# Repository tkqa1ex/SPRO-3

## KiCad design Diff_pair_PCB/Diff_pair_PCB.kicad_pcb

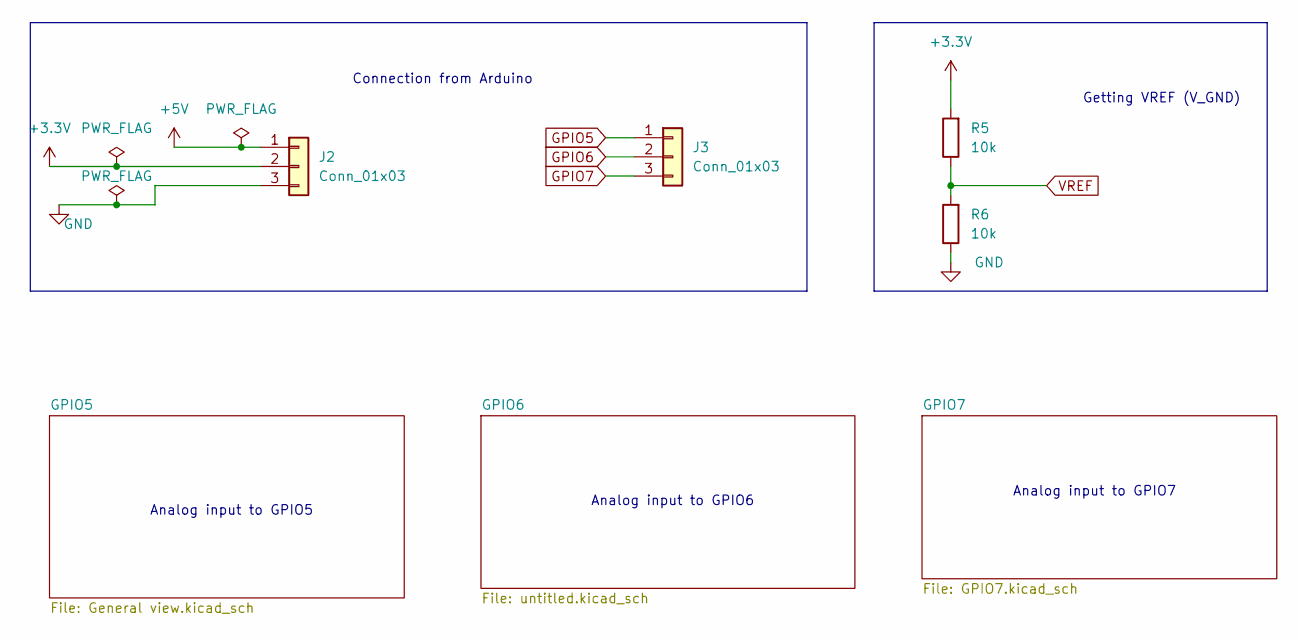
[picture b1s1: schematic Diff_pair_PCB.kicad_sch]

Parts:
J2, J3: Conn_01x03; PinHeader_1x03_P2.54mm_Vertical
R5, R6: 10k; R_Axial_DIN0207_L6.3mm_D2.5mm_P7.62mm_Horizontal

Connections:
+3.3V: J2.2, R5.2; also elsewhere on the board
+5V: J2.1; also elsewhere on the board
GND: J2.3, R6.1; also elsewhere on the board
GPIO5: J3.1; also elsewhere on the board
GPIO6: J3.2; also elsewhere on the board
GPIO7: J3.3; also elsewhere on the board
VREF: R5.1, R6.2; also elsewhere on the board

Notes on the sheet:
Analog input to GPIO7
Analog input to GPIO5
Connection from Arduino
Getting VREF (V_GND)
Analog input to GPIO6

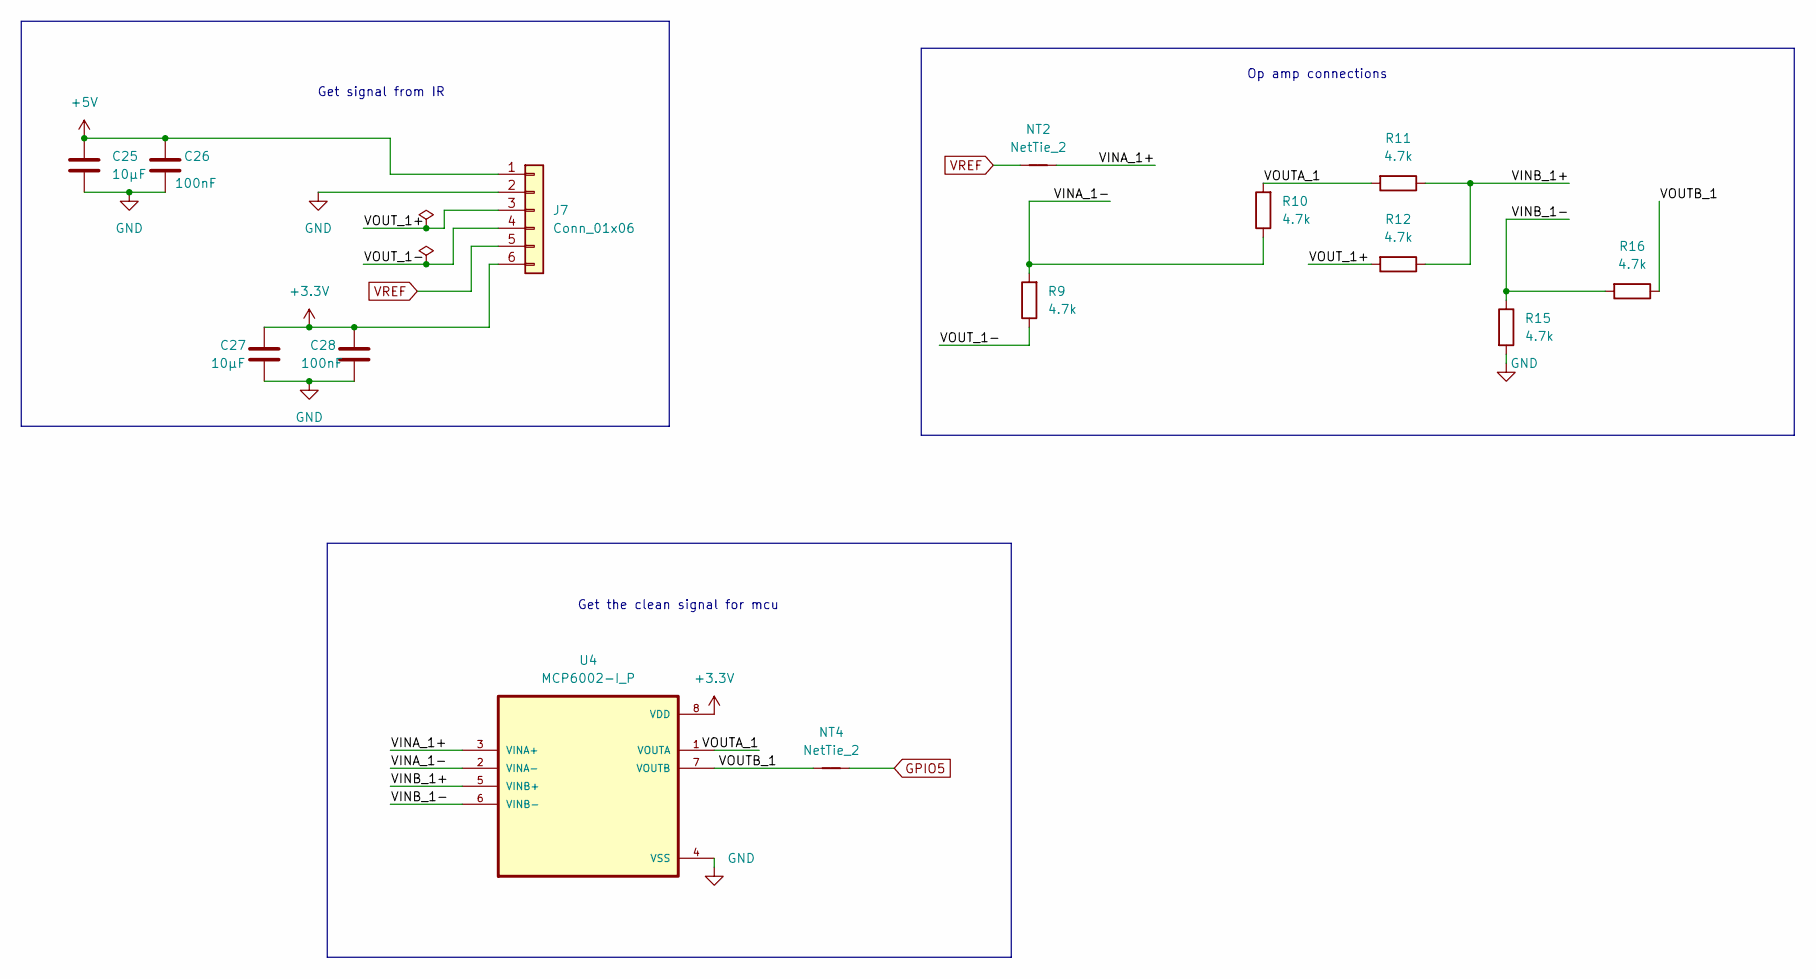
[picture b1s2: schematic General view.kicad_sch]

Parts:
C25, C27: 10µF; CP_Radial_D5.0mm_P2.00mm
C26, C28: 100nF; C_Disc_D5.0mm_W2.5mm_P5.00mm
J7: Conn_01x06; PinHeader_1x06_P2.54mm_Vertical
NT2, NT4: NetTie_2; NetTie-2_SMD_Pad0.3mm
R9, R10, R11, R12, R15, R16: 4.7k; R_Axial_DIN0207_L6.3mm_D2.5mm_P7.62mm_Horizontal
U4: MCP6002-I_P; DIP787W46P254L927H533Q8; MPN MCP6002-I/P

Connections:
+3.3V: C27.1, C28.1, J7.6, U4.8 (VDD); also elsewhere on the board
+5V: C25.1, C26.1, J7.1; also elsewhere on the board
/GPIO5/VINA_1+: NT2.2, U4.3 (VINA+)
/GPIO5/VINA_1-: R9.2, R10.1, U4.2 (VINA-)
/GPIO5/VINB_1+: R11.1, R12.1, U4.5 (VINB+)
/GPIO5/VINB_1-: R15.1, R16.2, U4.6 (VINB-)
/GPIO5/VOUTA_1: R10.2, R11.2, U4.1 (VOUTA)
/GPIO5/VOUTB_1: NT4.1, R16.1, U4.7 (VOUTB)
/GPIO5/VOUT_1+: J7.3, R12.2
/GPIO5/VOUT_1-: J7.4, R9.1
GND: C25.2, C26.2, C27.2, C28.2, J7.2, R15.2, U4.4 (VSS); also elsewhere on the board
GPIO5: NT4.2; also elsewhere on the board
VREF: J7.5, NT2.1; also elsewhere on the board

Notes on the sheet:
Op amp connections
Get signal from IR
Get the clean signal for mcu

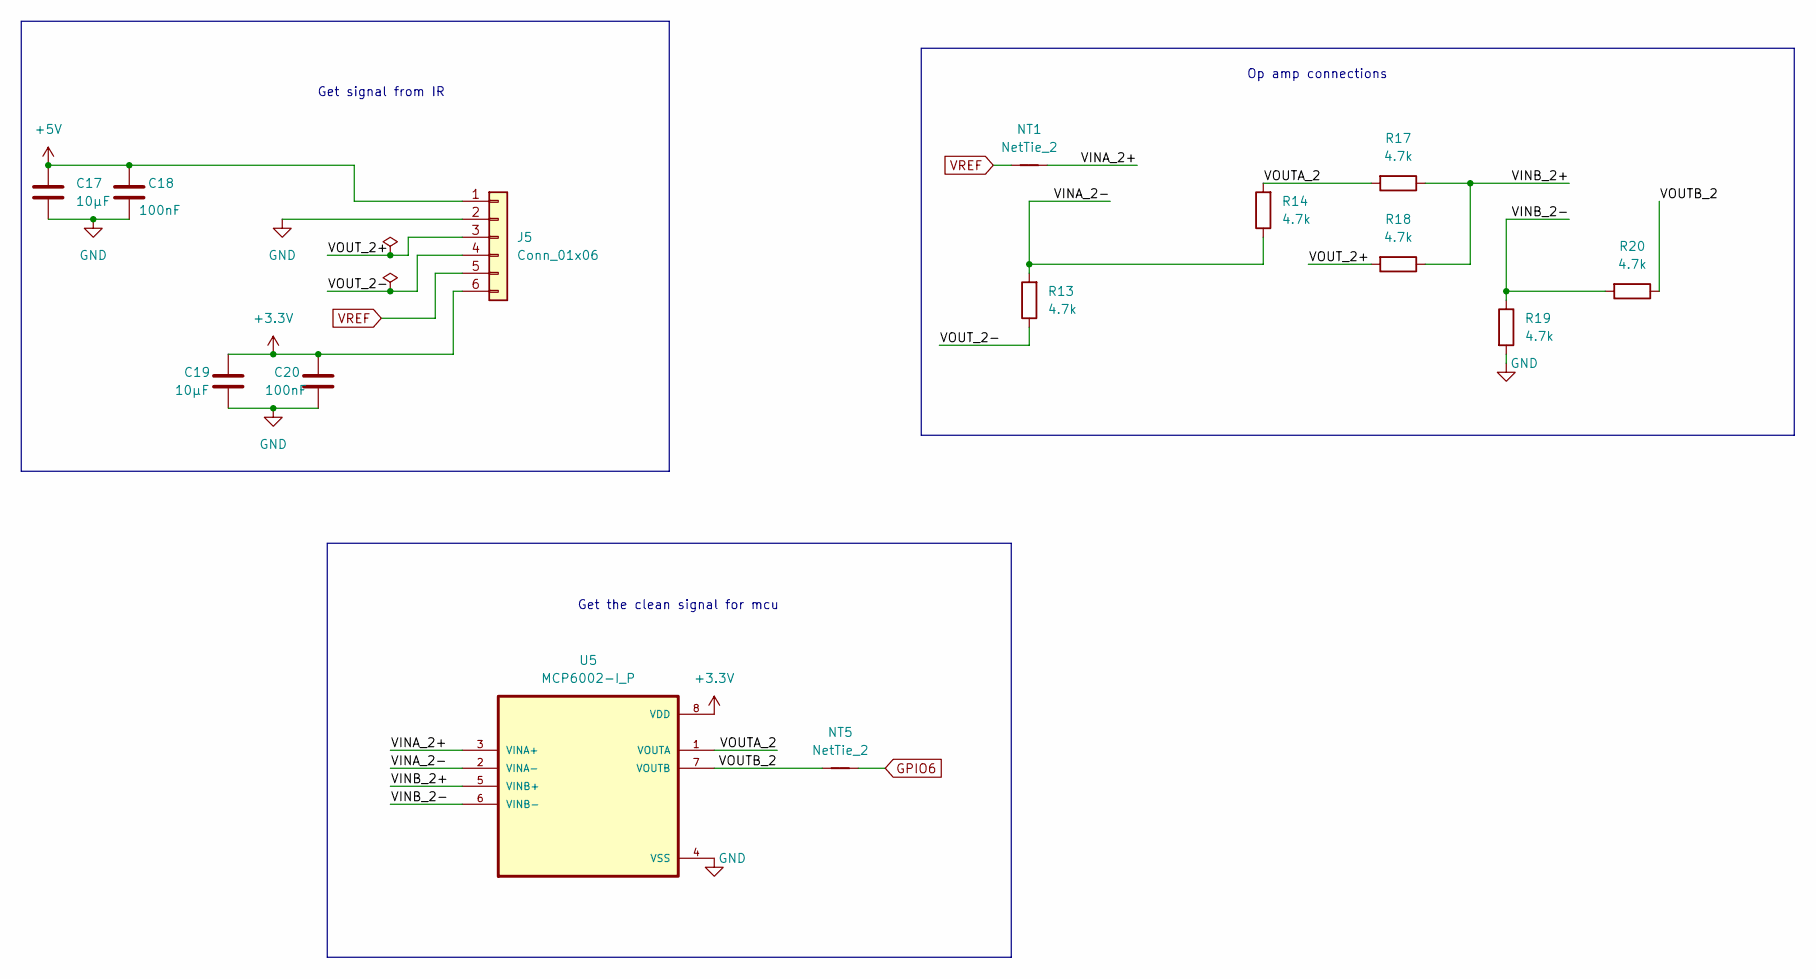
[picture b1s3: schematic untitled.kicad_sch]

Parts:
C17, C19: 10µF; CP_Radial_D5.0mm_P2.00mm
C18, C20: 100nF; C_Disc_D5.0mm_W2.5mm_P5.00mm
J5: Conn_01x06; PinHeader_1x06_P2.54mm_Vertical
NT1, NT5: NetTie_2; NetTie-2_SMD_Pad0.3mm
R13, R14, R17, R18, R19, R20: 4.7k; R_Axial_DIN0207_L6.3mm_D2.5mm_P7.62mm_Horizontal
U5: MCP6002-I_P; DIP787W46P254L927H533Q8; MPN MCP6002-I/P

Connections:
+3.3V: C19.1, C20.1, J5.6, U5.8 (VDD); also elsewhere on the board
+5V: C17.1, C18.1, J5.1; also elsewhere on the board
/GPIO6/VINA_2+: NT1.2, U5.3 (VINA+)
/GPIO6/VINA_2-: R13.2, R14.1, U5.2 (VINA-)
/GPIO6/VINB_2+: R17.1, R18.1, U5.5 (VINB+)
/GPIO6/VINB_2-: R19.1, R20.2, U5.6 (VINB-)
/GPIO6/VOUTA_2: R14.2, R17.2, U5.1 (VOUTA)
/GPIO6/VOUTB_2: NT5.1, R20.1, U5.7 (VOUTB)
/GPIO6/VOUT_2+: J5.3, R18.2
/GPIO6/VOUT_2-: J5.4, R13.1
GND: C17.2, C18.2, C19.2, C20.2, J5.2, R19.2, U5.4 (VSS); also elsewhere on the board
GPIO6: NT5.2; also elsewhere on the board
VREF: J5.5, NT1.1; also elsewhere on the board

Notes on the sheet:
Get the clean signal for mcu
Op amp connections
Get signal from IR

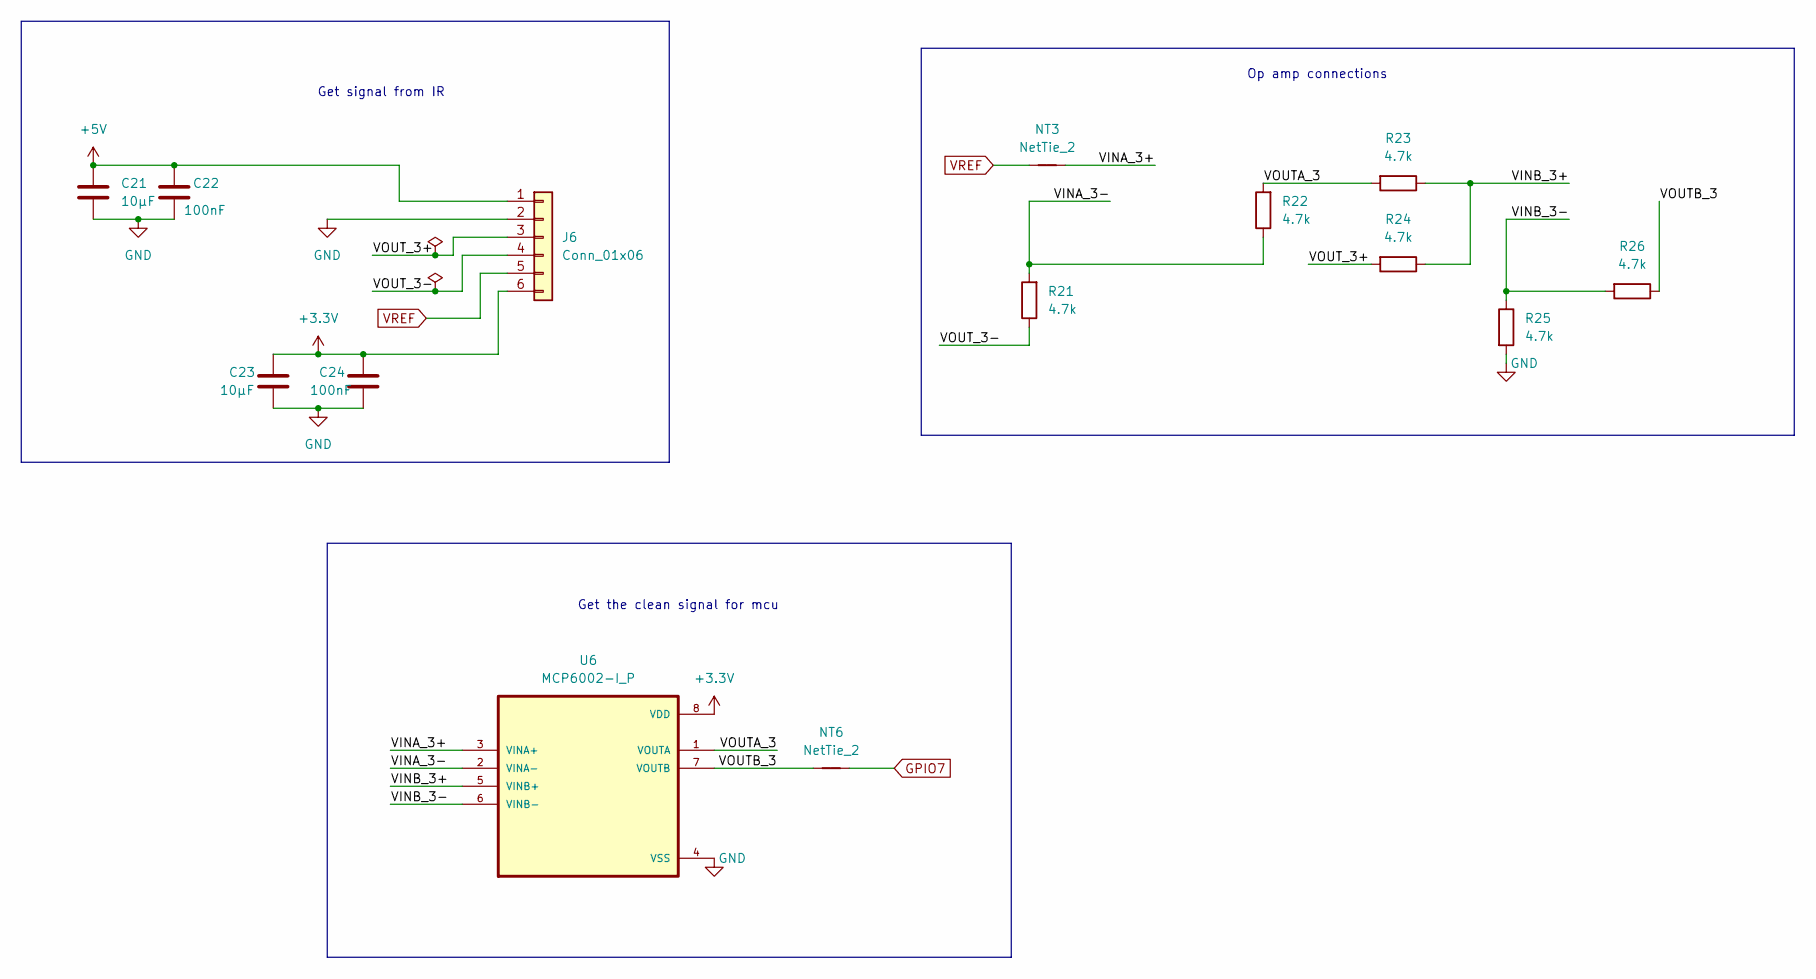
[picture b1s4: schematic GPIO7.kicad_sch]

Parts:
C21, C23: 10µF; CP_Radial_D5.0mm_P2.00mm
C22, C24: 100nF; C_Disc_D5.0mm_W2.5mm_P5.00mm
J6: Conn_01x06; PinHeader_1x06_P2.54mm_Vertical
NT3, NT6: NetTie_2; NetTie-2_SMD_Pad0.3mm
R21, R22, R23, R24, R25, R26: 4.7k; R_Axial_DIN0207_L6.3mm_D2.5mm_P7.62mm_Horizontal
U6: MCP6002-I_P; DIP787W46P254L927H533Q8; MPN MCP6002-I/P

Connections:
+3.3V: C23.1, C24.1, J6.6, U6.8 (VDD); also elsewhere on the board
+5V: C21.1, C22.1, J6.1; also elsewhere on the board
/GPIO7/VINA_3+: NT3.2, U6.3 (VINA+)
/GPIO7/VINA_3-: R21.2, R22.1, U6.2 (VINA-)
/GPIO7/VINB_3+: R23.1, R24.1, U6.5 (VINB+)
/GPIO7/VINB_3-: R25.1, R26.2, U6.6 (VINB-)
/GPIO7/VOUTA_3: R22.2, R23.2, U6.1 (VOUTA)
/GPIO7/VOUTB_3: NT6.1, R26.1, U6.7 (VOUTB)
/GPIO7/VOUT_3+: J6.3, R24.2
/GPIO7/VOUT_3-: J6.4, R21.1
GND: C21.2, C22.2, C23.2, C24.2, J6.2, R25.2, U6.4 (VSS); also elsewhere on the board
GPIO7: NT6.2; also elsewhere on the board
VREF: J6.5, NT3.1; also elsewhere on the board

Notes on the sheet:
Get the clean signal for mcu
Get signal from IR
Op amp connections

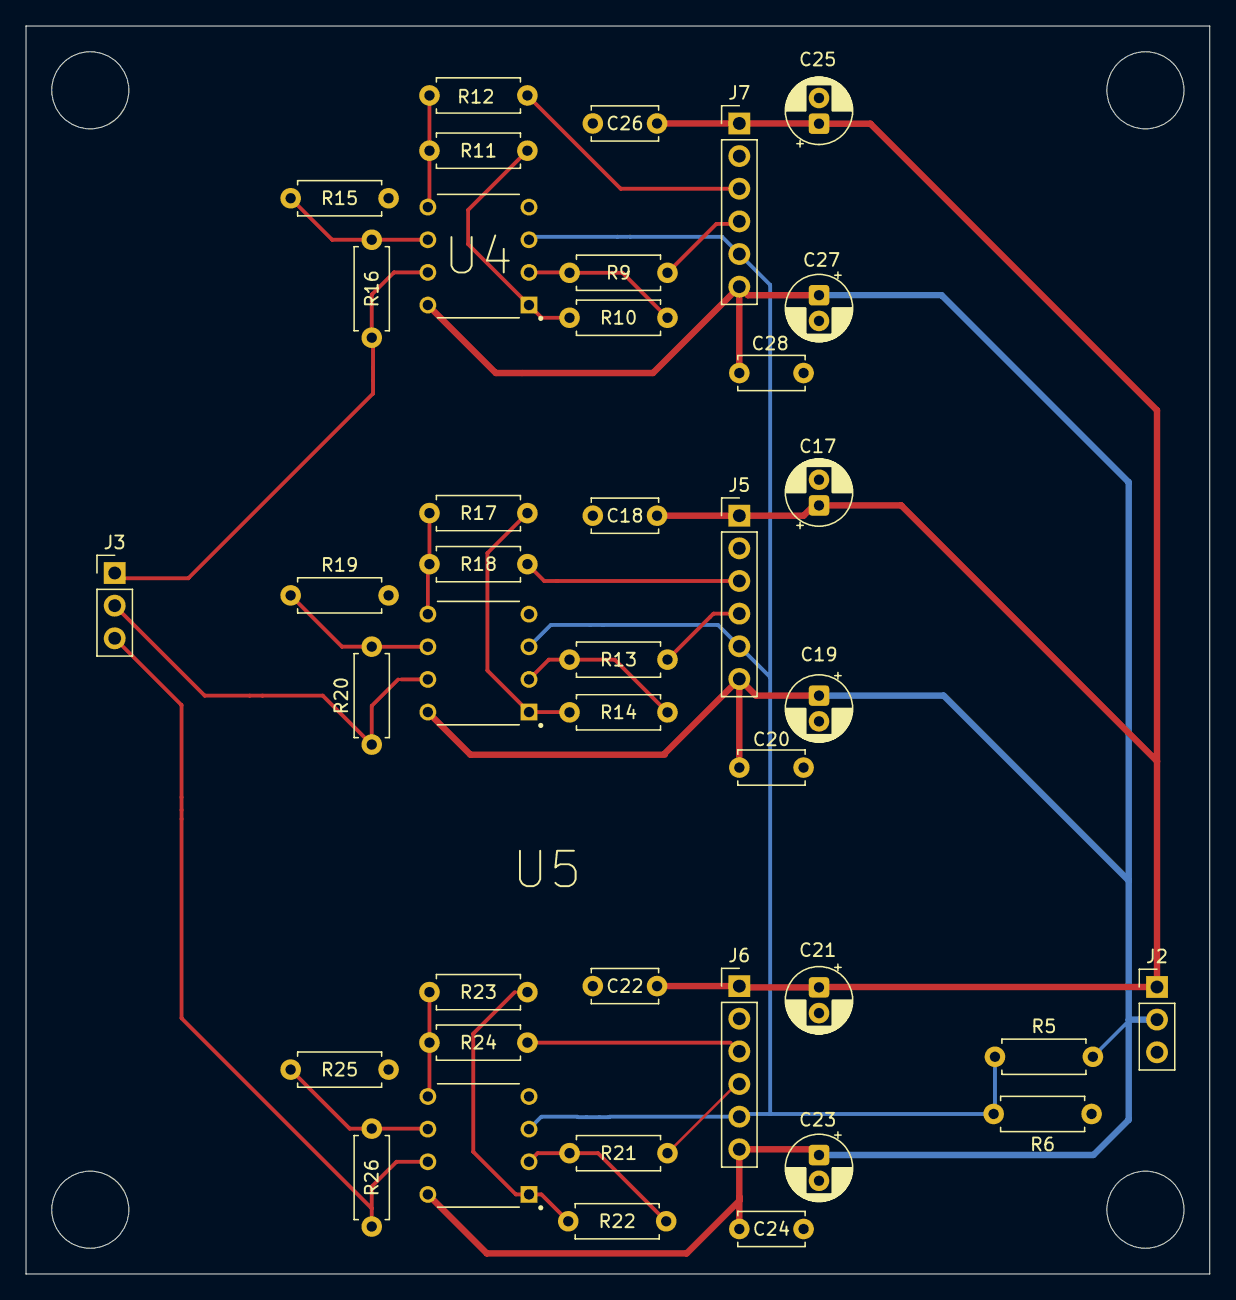
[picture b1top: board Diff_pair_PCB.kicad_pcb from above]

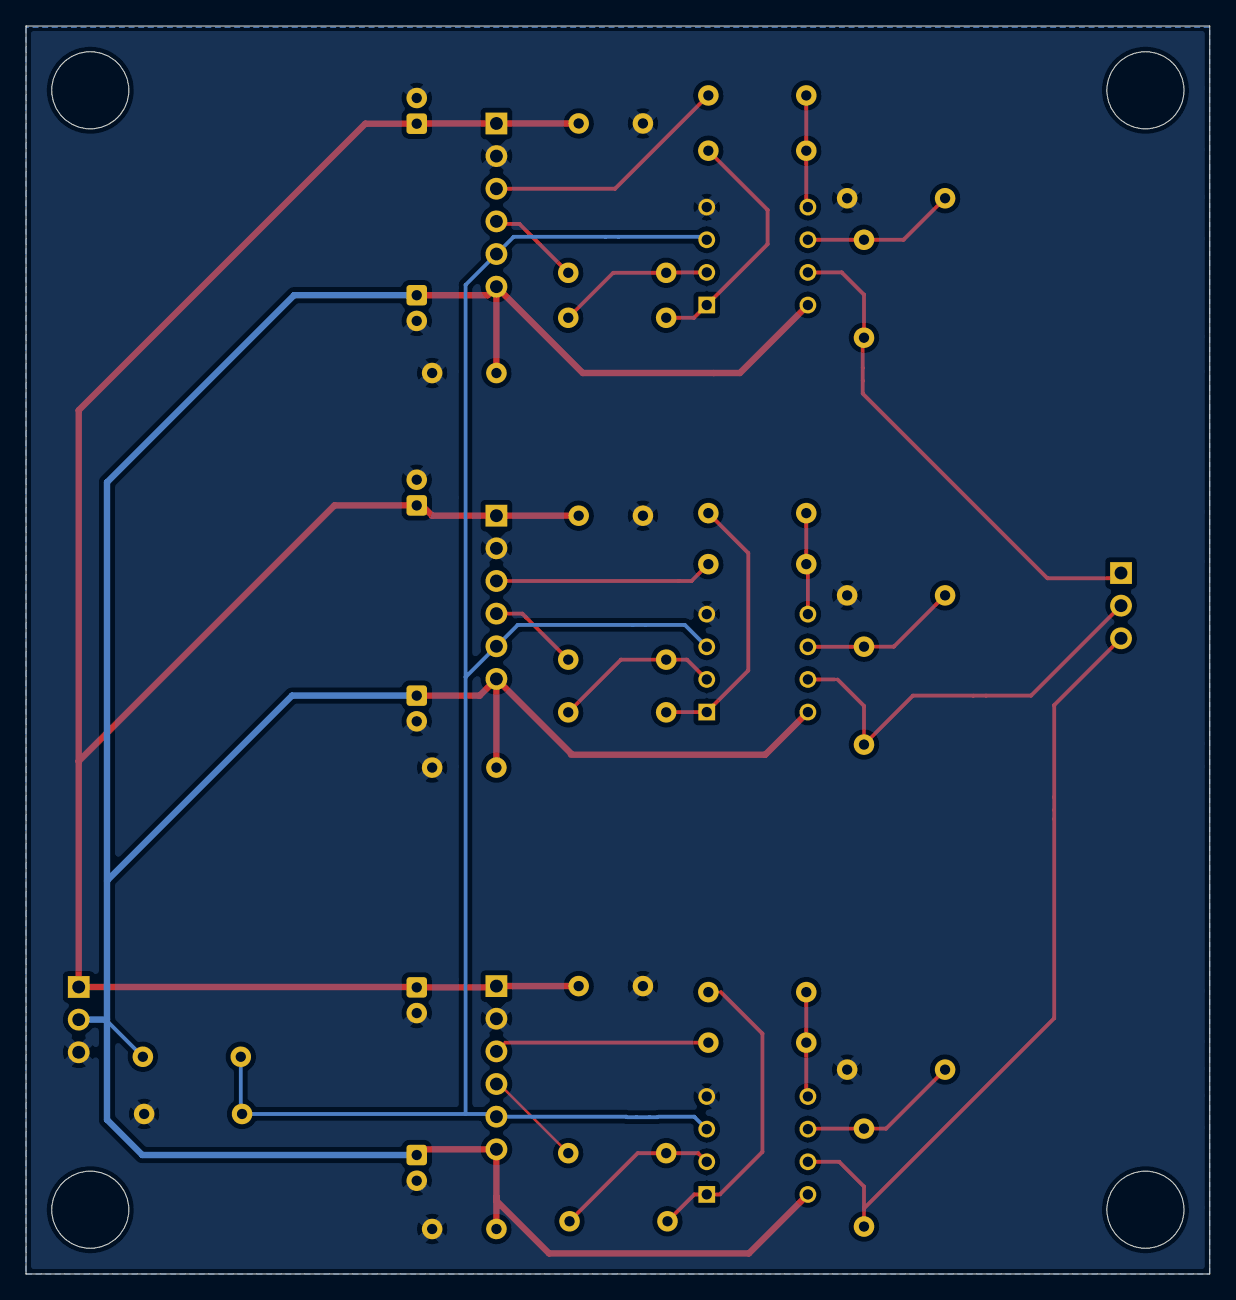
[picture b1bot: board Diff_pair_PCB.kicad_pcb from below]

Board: 2 copper layers, 92.1 x 97.1 mm, 46 parts (3 on the bottom side), 31 nets.

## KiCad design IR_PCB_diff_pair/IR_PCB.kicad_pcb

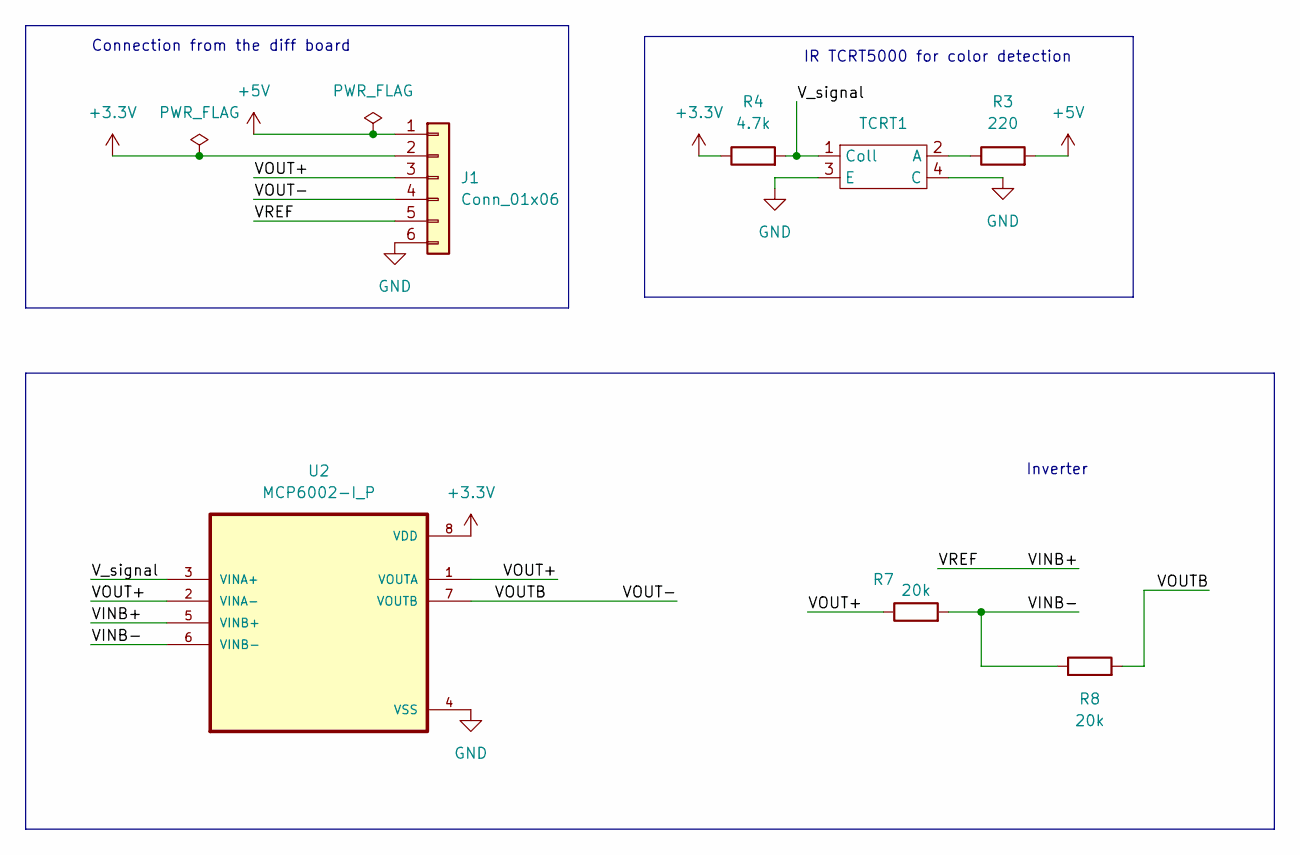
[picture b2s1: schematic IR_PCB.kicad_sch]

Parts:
J1: Conn_01x06; PinHeader_1x06_P2.54mm_Vertical
R3: 220; R_Axial_DIN0207_L6.3mm_D2.5mm_P7.62mm_Horizontal
R4: 4.7k; R_Axial_DIN0207_L6.3mm_D2.5mm_P7.62mm_Horizontal
R7, R8: 20k; R_Axial_DIN0207_L6.3mm_D2.5mm_P7.62mm_Horizontal
TCRT1: TCRT5000L
U2: MCP6002-I_P; DIP787W46P254L927H533Q8; MPN MCP6002-I/P

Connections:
+3.3V: J1.2, R4.1, U2.8 (VDD)
+5V: J1.1, R3.2
/VINB+: J1.5, U2.5 (VINB+)
/VINB-: R7.2, R8.1, U2.6 (VINB-)
/VOUT+: J1.3, R7.1, U2.1 (VOUTA), U2.2 (VINA-)
/VOUT-: J1.4, R8.2, U2.7 (VOUTB)
/V_signal: R4.2, TCRT1.1 (Coll), U2.3 (VINA+)
GND: J1.6, TCRT1.3 (E), TCRT1.4 (C), U2.4 (VSS)
unnamed: R3.1, TCRT1.2 (A)

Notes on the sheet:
Inverter
Connection from the diff board
IR TCRT5000 for color detection

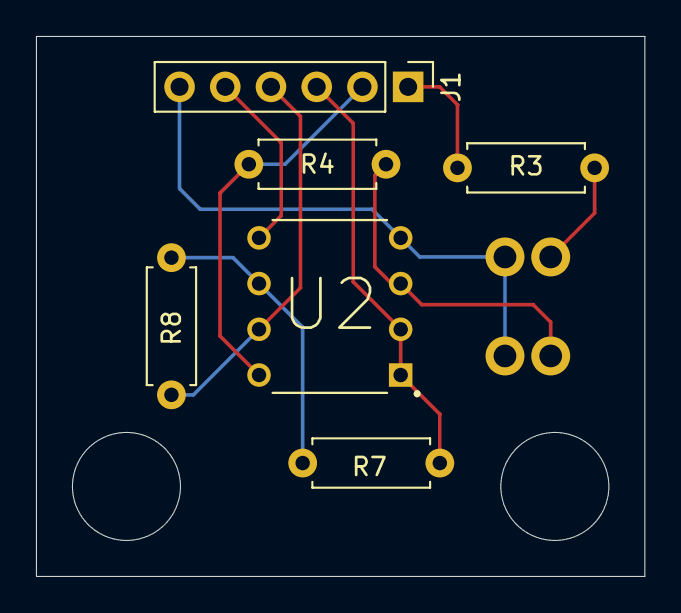
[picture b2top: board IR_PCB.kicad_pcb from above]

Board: 2 copper layers, 33.8 x 30.0 mm, 7 parts (1 on the bottom side), 9 nets.

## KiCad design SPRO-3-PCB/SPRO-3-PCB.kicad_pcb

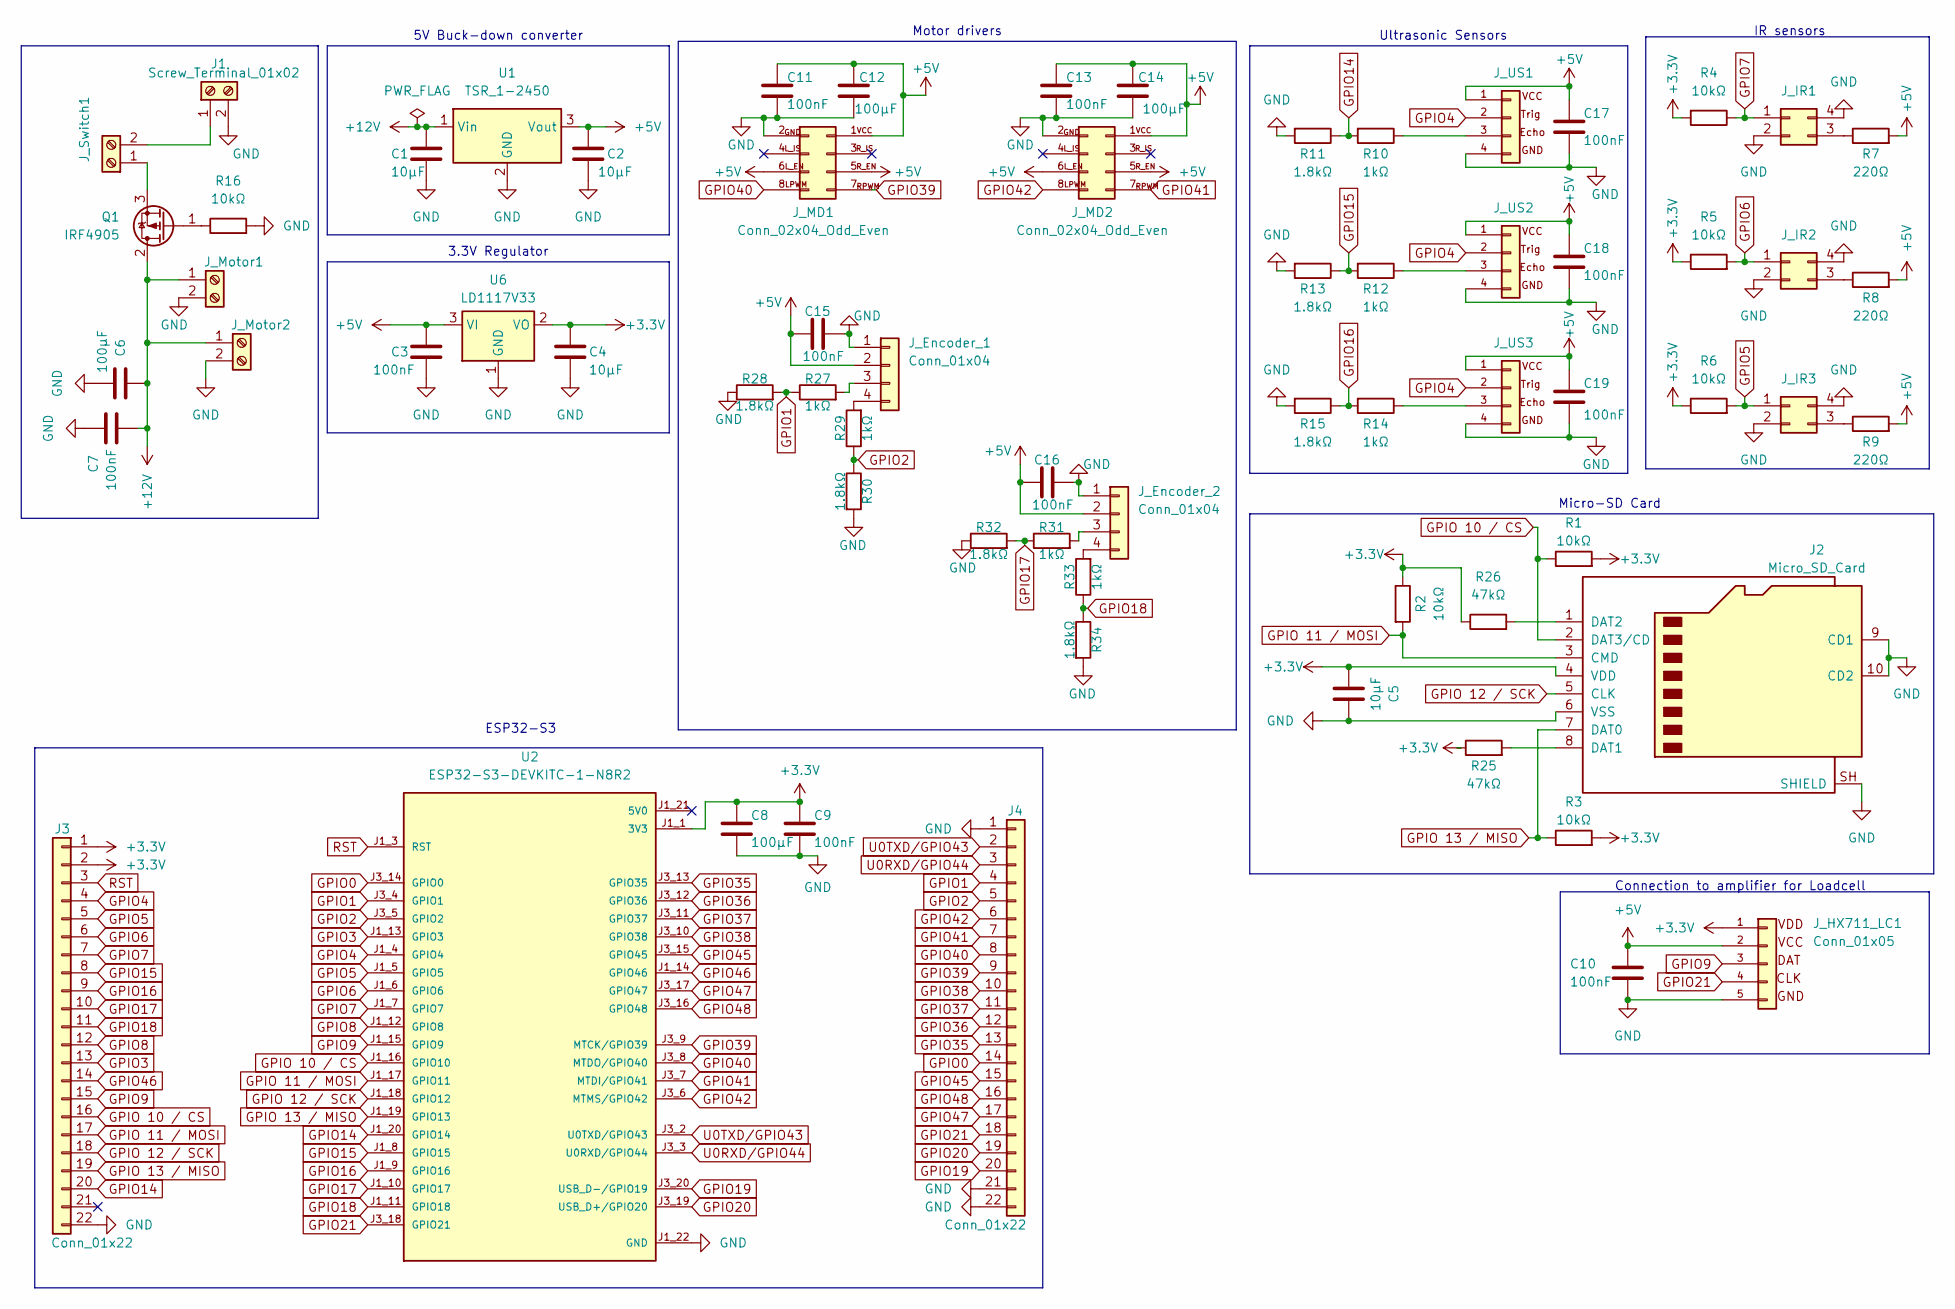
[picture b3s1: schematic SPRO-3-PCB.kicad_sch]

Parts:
C1, C2, C4, C5: 10µF; CP_Radial_D5.0mm_P2.00mm
C3, C7, C9, C10, C11, C13, C15, C16, C17, C18, C19: 100nF; C_Disc_D5.0mm_W2.5mm_P5.00mm
C6, C8, C12, C14: 100µF; CP_Radial_D6.3mm_P2.50mm
J1: Screw_Terminal_01x02; TerminalBlock_Phoenix_MKDS-1,5-2-5.08_1x02_P5.08mm_Horizont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
J2: Micro_SD_Card; microSD_HC_Molex_104031-0811
J3, J4: Conn_01x22; PinHeader_1x22_P2.54mm_Vertical
J_Encoder_1, J_Encoder_2: Conn_01x04; PinHeader_1x04_P2.54mm_Vertical
J_HX711_LC1: Conn_01x05; PinHeader_1x05_P2.54mm_Vertical
J_IR1: IR-1; PinHeader_2x02_P2.54mm_Vertical
J_IR2: IR-2; PinHeader_2x02_P2.54mm_Vertical
J_IR3: Conn_02x02; PinHeader_2x02_P2.54mm_Vertical
J_MD1, J_MD2: Conn_02x04_Odd_Even; PinHeader_2x04_P2.54mm_Vertical
J_Motor1, J_Motor2: Screw_Terminal_01x02; TerminalBlock_Phoenix_MKDS-1,5-2-5.08_1x02_P5.08mm_Horizont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
J_Switch1: Screw_Terminal_01x02; TerminalBlock_Phoenix_MKDS-1,5-2-5.08_1x02_P5.08mm_Horizont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
J_US1, J_US2, J_US3: PinHeader_1x04_P2.54mm_Vertical
Q1: IRF4905; TO-220-3_Vertical
R1, R2, R3, R4, R5, R6, R16: 10kΩ; R_Axial_DIN0207_L6.3mm_D2.5mm_P7.62mm_Horizontal
R7, R8, R9: 220Ω; R_Axial_DIN0207_L6.3mm_D2.5mm_P7.62mm_Horizontal
R10, R12, R14, R27, R29, R31, R33: 1kΩ; R_Axial_DIN0207_L6.3mm_D2.5mm_P7.62mm_Horizontal
R11, R13, R15, R28, R30, R32, R34: 1.8kΩ; R_Axial_DIN0207_L6.3mm_D2.5mm_P7.62mm_Horizontal
R25, R26: 47kΩ; R_Axial_DIN0207_L6.3mm_D2.5mm_P7.62mm_Horizontal
U1: TSR_1-2450; Converter_DCDC_TRACO_TSR-1_THT
U2: ESP32-S3-DEVKITC-1-N8R2; XCVR_ESP32-S3-DEVKITC-1-N8R2; PARTREV V1
U6: LD1117V33; TO-220-3_Vertical

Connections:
+3.3V: C4.1, C5.1, C8.1, C9.1, J2.4 (VDD), J3.1, J3.2, J_HX711_LC1.1, R1.2, R2.1, R3.2, R4.2, R5.1, R6.1, R25.1, R26.1, U2.J1_1 (3V3), U2.J1_2 (3V3), U6.2 (VO)
+5V: C2.1, C3.1, C10.2, C11.1, C12.1, C13.1, C14.1, C15.1, C16.1, C17.1, C18.1, C19.1, J_Encoder_1.2, J_Encoder_2.2, J_HX711_LC1.2, J_MD1.1 (Pin_2), J_MD1.5 (Pin_6), J_MD1.6 (Pin_5), J_MD2.1 (Pin_2), J_MD2.5 (Pin_6), J_MD2.6 (Pin_5), J_US1.1, J_US2.1, J_US3.1, R7.2, R8.2, R9.2, U1.3 (Vout), U6.3 (VI)
+12V: C1.1, C6.2, C7.1, J_Motor1.1, J_Motor2.1, Q1.2 (D), U1.1 (Vin)
GND: C1.2, C2.2, C3.2, C4.2, C5.2, C6.1, C7.2, C8.2, C9.2, C10.1, C11.2, C12.2, C13.2, C14.2, C15.2, C16.2, C17.2, C18.2, C19.2, J1.2, J2.6 (VSS), J2.9 (CD1), J2.10 (CD2), J2.SH (SHIELD), J3.22, J4.1, J4.21, J4.22, J_Encoder_1.1, J_Encoder_2.1, J_HX711_LC1.5, J_IR1.2, J_IR1.4, J_IR2.2, J_IR2.4, J_IR3.2, J_IR3.4, J_MD1.2 (Pin_1), J_MD2.2 (Pin_1), J_Motor1.2, J_Motor2.2, J_US1.4, J_US2.4, J_US3.4, R11.2, R13.2, R15.2, R16.2, R28.1, R30.2, R32.1, R34.2, U1.2 (GND), U2.J1_22 (GND), U2.J3_1 (GND), U2.J3_21 (GND), U2.J3_22 (GND), U6.1 (GND)
GPIO0: J4.14, U2.J3_14 (GPIO0)
GPIO1: J4.4, R27.1, R28.2, U2.J3_4 (GPIO1)
GPIO2: J4.5, R29.1, R30.1, U2.J3_5 (GPIO2)
GPIO3: J3.13, U2.J1_13 (GPIO3)
GPIO4: J3.4, J_US1.2, J_US2.2, J_US3.2, U2.J1_4 (GPIO4)
GPIO5: J3.5, J_IR3.1, R6.2, U2.J1_5 (GPIO5)
GPIO6: J3.6, J_IR2.1, R5.2, U2.J1_6 (GPIO6)
GPIO7: J3.7, J_IR1.1, R4.1, U2.J1_7 (GPIO7)
GPIO8: J3.12, U2.J1_12 (GPIO8)
GPIO9: J3.15, J_HX711_LC1.3, U2.J1_15 (GPIO9)
GPIO14: J3.20, R10.2, R11.1, U2.J1_20 (GPIO14)
GPIO15: J3.8, R12.2, R13.1, U2.J1_8 (GPIO15)
GPIO16: J3.9, R14.2, R15.1, U2.J1_9 (GPIO16)
GPIO17: J3.10, R31.1, R32.2, U2.J1_10 (GPIO17)
GPIO18: J3.11, R33.1, R34.1, U2.J1_11 (GPIO18)
GPIO19: J4.20, U2.J3_20 (USB_D-/GPIO19)
GPIO20: J4.19, U2.J3_19 (USB_D+/GPIO20)
GPIO21: J4.18, J_HX711_LC1.4, U2.J3_18 (GPIO21)
GPIO35: J4.13, U2.J3_13 (GPIO35)
GPIO36: J4.12, U2.J3_12 (GPIO36)
GPIO37: J4.11, U2.J3_11 (GPIO37)
GPIO38: J4.10, U2.J3_10 (GPIO38)
GPIO39: J4.9, J_MD1.7 (Pin_8), U2.J3_9 (MTCK/GPIO39)
GPIO40: J4.8, J_MD1.8 (Pin_7), U2.J3_8 (MTDO/GPIO40)
GPIO41: J4.7, J_MD2.7 (Pin_8), U2.J3_7 (MTDI/GPIO41)
GPIO42: J4.6, J_MD2.8 (Pin_7), U2.J3_6 (MTMS/GPIO42)
GPIO45: J4.15, U2.J3_15 (GPIO45)
GPIO46: J3.14, U2.J1_14 (GPIO46)
GPIO47: J4.17, U2.J3_17 (GPIO47)
GPIO48: J4.16, U2.J3_16 (GPIO48)
GPIO 10 / CS: J2.2 (DAT3/CD), J3.16, R1.1, U2.J1_16 (GPIO10)
GPIO 11 / MOSI: J2.3 (CMD), J3.17, R2.2, U2.J1_17 (GPIO11)
GPIO 12 / SCK: J2.5 (CLK), J3.18, U2.J1_18 (GPIO12)
GPIO 13 / MISO: J2.7 (DAT0), J3.19, R3.1, U2.J1_19 (GPIO13)
unnamed: J1.1, J_Switch1.2
unnamed: J2.8 (DAT1), R25.2
unnamed: J2.1 (DAT2), R26.2
unnamed: J_Encoder_1.3, R27.2
unnamed: J_Encoder_1.4, R29.2
unnamed: J_Encoder_2.3, R31.2
unnamed: J_Encoder_2.4, R33.2
unnamed: J_IR1.3, R7.1
unnamed: J_IR2.3, R8.1
unnamed: J_IR3.3, R9.1
unnamed: J_Switch1.1, Q1.3 (S)
unnamed: J_US1.3, R10.1
unnamed: J_US2.3, R12.1
unnamed: J_US3.3, R14.1
unnamed: Q1.1 (G), R16.1
RST: J3.3, U2.J1_3 (RST)
U0RXD/GPIO44: J4.3, U2.J3_3 (U0RXD/GPIO44)
U0TXD/GPIO43: J4.2, U2.J3_2 (U0TXD/GPIO43)

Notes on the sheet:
IR sensors
Motor drivers
5V Buck-down converter
Micro-SD Card
Ultrasonic Sensors
Connection to amplifier for Loadcell
ESP32-S3
3.3V Regulator

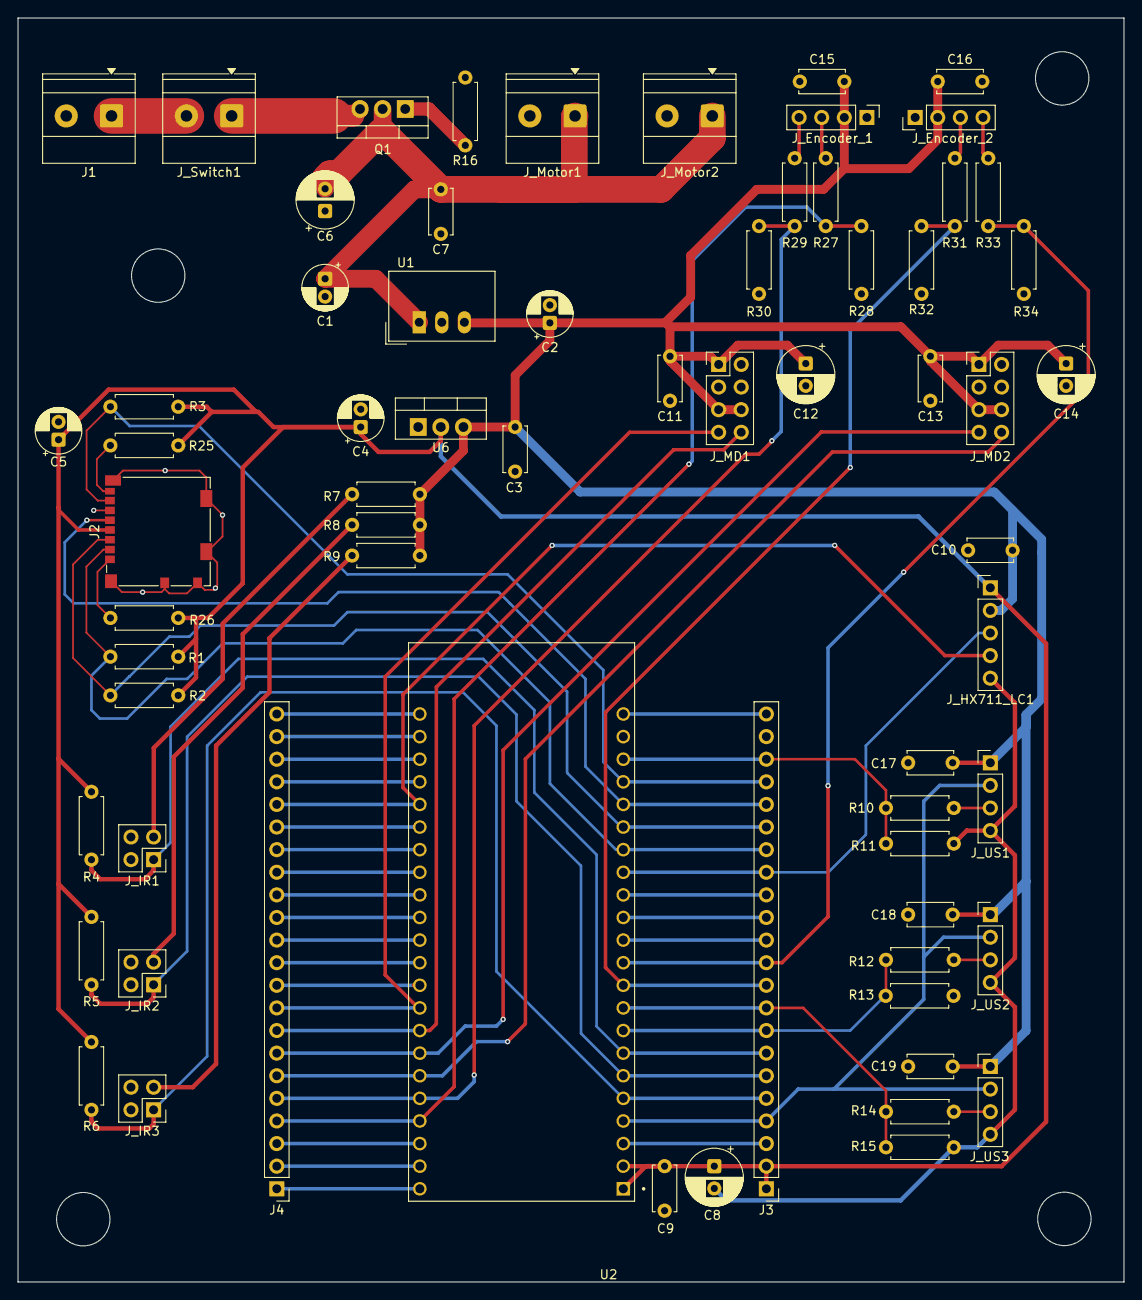
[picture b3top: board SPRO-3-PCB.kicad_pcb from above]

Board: 2 copper layers, 124.2 x 142.0 mm, 67 parts (0 on the bottom side), 56 nets.

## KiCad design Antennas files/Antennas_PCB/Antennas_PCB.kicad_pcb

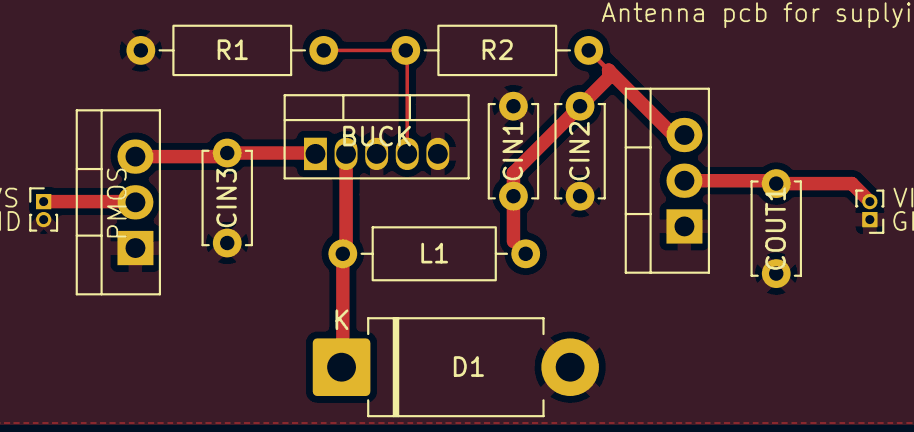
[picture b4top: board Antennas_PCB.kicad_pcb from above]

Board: 2 copper layers, 13 parts (0 on the bottom side), 7 nets.

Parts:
BUCK: LM2576T-ADJ; TO-220-5_Vertical
CIN1: 1000uF; C_Disc_D5.0mm_W2.5mm_P5.00mm
CIN2: 100nF; C_Disc_D5.0mm_W2.5mm_P5.00mm
CIN3: 100uF; C_Disc_D5.0mm_W2.5mm_P5.00mm
COUT1: 10uF; C_Disc_D5.0mm_W2.5mm_P5.00mm
D1: 1N5822; D_DO-201AD_P12.70mm_Horizontal
J1, J2: Conn_01x02_Pin; PinHeader_1x02_P1.00mm_Vertical
L1: 100uH; L_Axial_L6.6mm_D2.7mm_P10.16mm_Horizontal_Vishay_IM-2
PMOS: PMOS; Untitled
R1: 20kO; R_Axial_DIN0207_L6.3mm_D2.5mm_P10.16mm_Horizontal
R2: 62kO; R_Axial_DIN0207_L6.3mm_D2.5mm_P10.16mm_Horizontal
U2: LD1117V33; TO-220-3_Vertical

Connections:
/FB: BUCK.4 (FB), R1.1, R2.2
/OUT: BUCK.2 (OUT), D1.1 (K), L1.1
/VIN: BUCK.1 (VIN), CIN3.1, PMOS.3 (S)
/V_OUT(3.3V): COUT1.1, J2.2, U2.2 (VO)
/V_OUT_BUCK(5V): CIN1.1, CIN2.1, L1.2, R2.1, U2.3 (VI)
GND: BUCK.3 (GND), BUCK.5 (~ON/OFF), CIN1.2, CIN2.2, CIN3.2, COUT1.2, D1.2 (A), J1.2, J2.1, PMOS.2 (G), R1.2, U2.1 (GND)
unnamed: J1.1, PMOS.1 (D)
